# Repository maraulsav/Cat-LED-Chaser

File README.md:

# Cat-LED-Chaser
Hii! This is a cat shaped LED chaser. I wanted to make it as a keychain to be gifted to someone special for me during my highschool graduation later..
This is the final form of my cat LED casher

And here's the youtube video of my journey making this cat LED casher: https://www.youtube.com/watch?v=RgV0-7eemWM
See full built documentation at JOURNAL (1).md

## 3D View
Front

Back

## Features
- NE555P (555 Timer)
- CD4017 (Integrated Circuit)
- 10 LEDs
- 2 Capacitor
- 2 Resistor
- 1 Variable Resistor
- 1 Slide witch
- 1 Battery Socket
- 1 Battery

## PCB
My PCB is made in KiCad These are the footprints I used
- Battery: Battery_Panasonic_CR2032-HFN_Horizontal_CircularHoles
- Capacitor_THT:CP_Radial D5.0mm_P2.00mm
- LED_THT:LED_D3.0mm
- Resistor_THT:R_Axial_DIN0207_L6.3mm_D2.5mm_P7.62mm_Horizontal
- Variable Resistor: Potentiometer_THT: Potentiometer_Vishay_T93YA_Vertical
- SW SPST: Button_Switch_THT_SPST:SW_Push_1P2T_Vertical_E-Switch_800UDP8P1A1M6
- TestPoint: Connector PinSocket 2.54mm:PinSocket 1x01 P2.54mm Vertical
- NE555P: Package_DIP: DIP-8_W7.62mm
- 4017: footprints: N16

Here is my schematic:

and my PCB:

## BOM
You can see the BOM in Blinky Board-bom.csv files

## Additional Thingy
Thankyou for HackClub and  KiCad for making this project possible

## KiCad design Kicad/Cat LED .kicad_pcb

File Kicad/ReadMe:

Here's all the KiCad files. 
If you want to built your own LED chaser you can use my schematic design here!

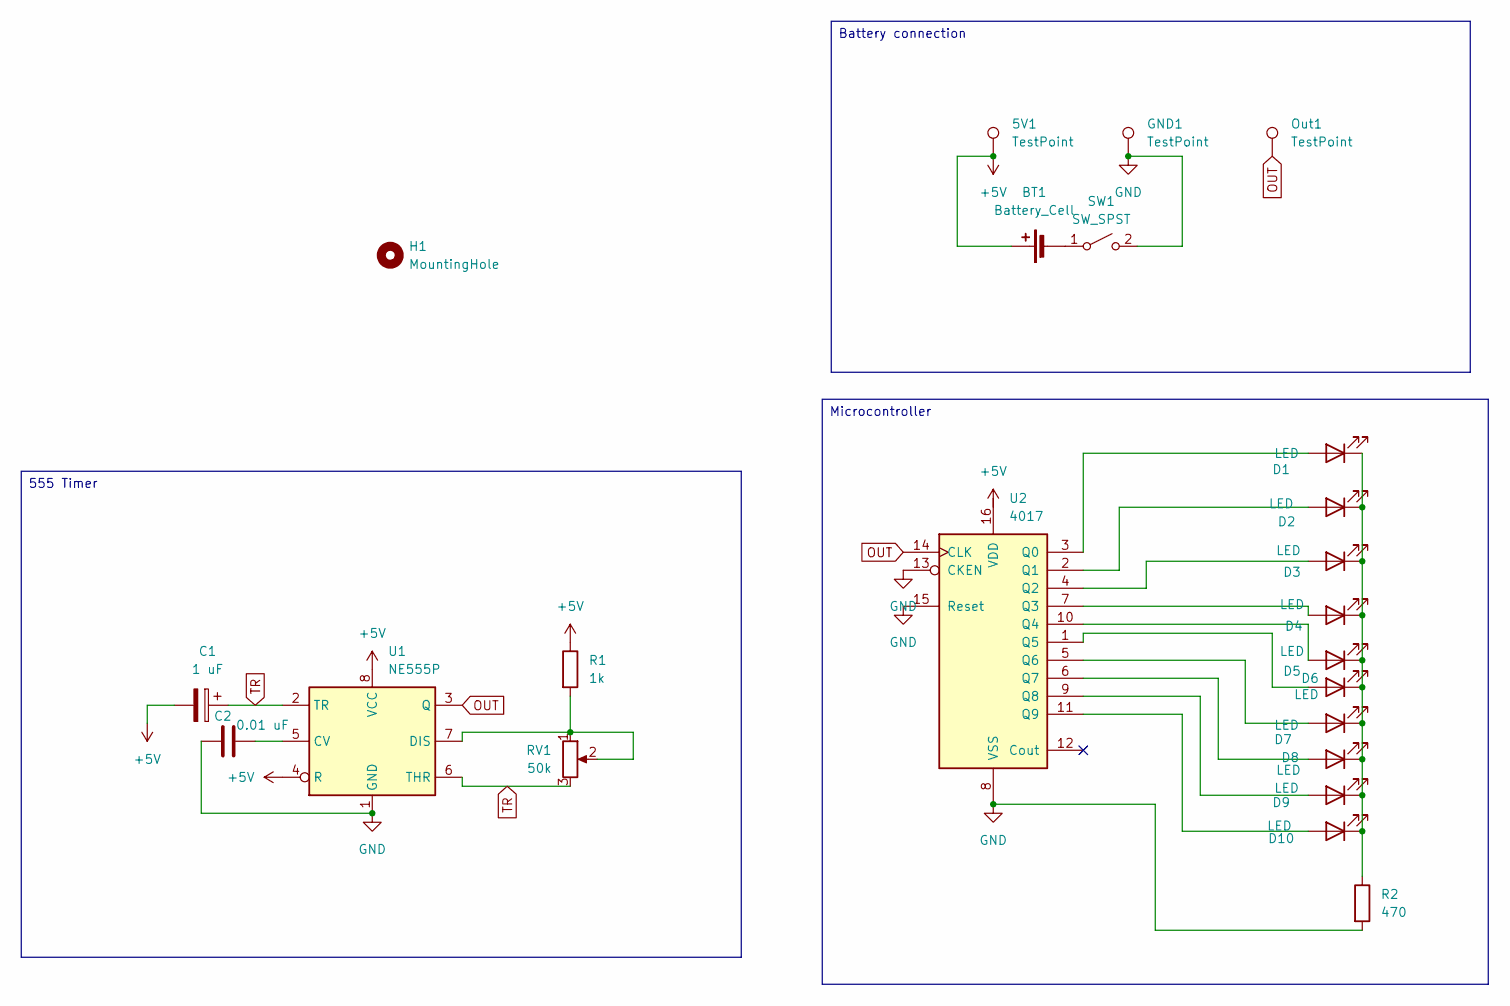
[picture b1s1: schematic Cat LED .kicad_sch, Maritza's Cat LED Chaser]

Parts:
5V1: TestPoint; PinSocket_1x01_P2.54mm_Vertical
BT1: Battery_Cell; Battery_Panasonic_CR2032-HFN_Horizontal_CircularHoles
C1: 1 uF; CP_Radial_D5.0mm_P2.00mm
C2: 0.01 uF; CP_Radial_D5.0mm_P2.00mm
D1, D2, D3, D4, D5, D6, D7, D8, D9, D10: LED; LED_D3.0mm
GND1: TestPoint; PinSocket_1x01_P2.54mm_Vertical
H1: MountingHole; MountingHole_4mm
Out1: TestPoint; PinSocket_1x01_P2.54mm_Vertical
R1: 1k; R_Axial_DIN0207_L6.3mm_D2.5mm_P7.62mm_Horizontal
R2: 470; R_Axial_DIN0207_L6.3mm_D2.5mm_P7.62mm_Horizontal
RV1: 50k; Potentiometer_Vishay_T93YA_Vertical
SW1: SW_SPST; SW_Push_1P2T_Vertical_E-Switch_800UDP8P1A1M6
U1: NE555P; DIP-8_W7.62mm
U2: 4017; N16

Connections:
+5V: 5V1.1, BT1.1 (+), C1.2, R1.1, U1.4 (R), U1.8 (VCC)
GND: C2.2, GND1.1, R2.2, SW1.2 (B), U1.1 (GND), U2.8 (VSS), U2.13 (CKEN), U2.15 (Reset)
unnamed: BT1.2 (-), SW1.1 (A)
unnamed: D1.2 (A), U2.3 (Q0)
unnamed: D1.1 (K), D2.1 (K), D3.1 (K), D4.1 (K), D5.1 (K), D6.1 (K), D7.1 (K), D8.1 (K), D9.1 (K), D10.1 (K), R2.1
unnamed: D2.2 (A), U2.2 (Q1)
unnamed: D3.2 (A), U2.4 (Q2)
unnamed: D4.2 (A), U2.7 (Q3)
unnamed: D5.2 (A), U2.10 (Q4)
unnamed: D6.2 (A), U2.1 (Q5)
unnamed: D7.2 (A), U2.5 (Q6)
unnamed: D8.2 (A), U2.6 (Q7)
unnamed: D9.2 (A), U2.9 (Q8)
unnamed: D10.2 (A), U2.11 (Q9)
unnamed: C2.1, U1.5 (CV)
unnamed: R1.2, RV1.1, RV1.2, U1.7 (DIS)
OUT: Out1.1, U1.3 (Q), U2.14 (CLK)
TR: C1.1, RV1.3, U1.2 (TR), U1.6 (THR)

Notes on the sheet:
Microcontroller
Battery connection
555 Timer

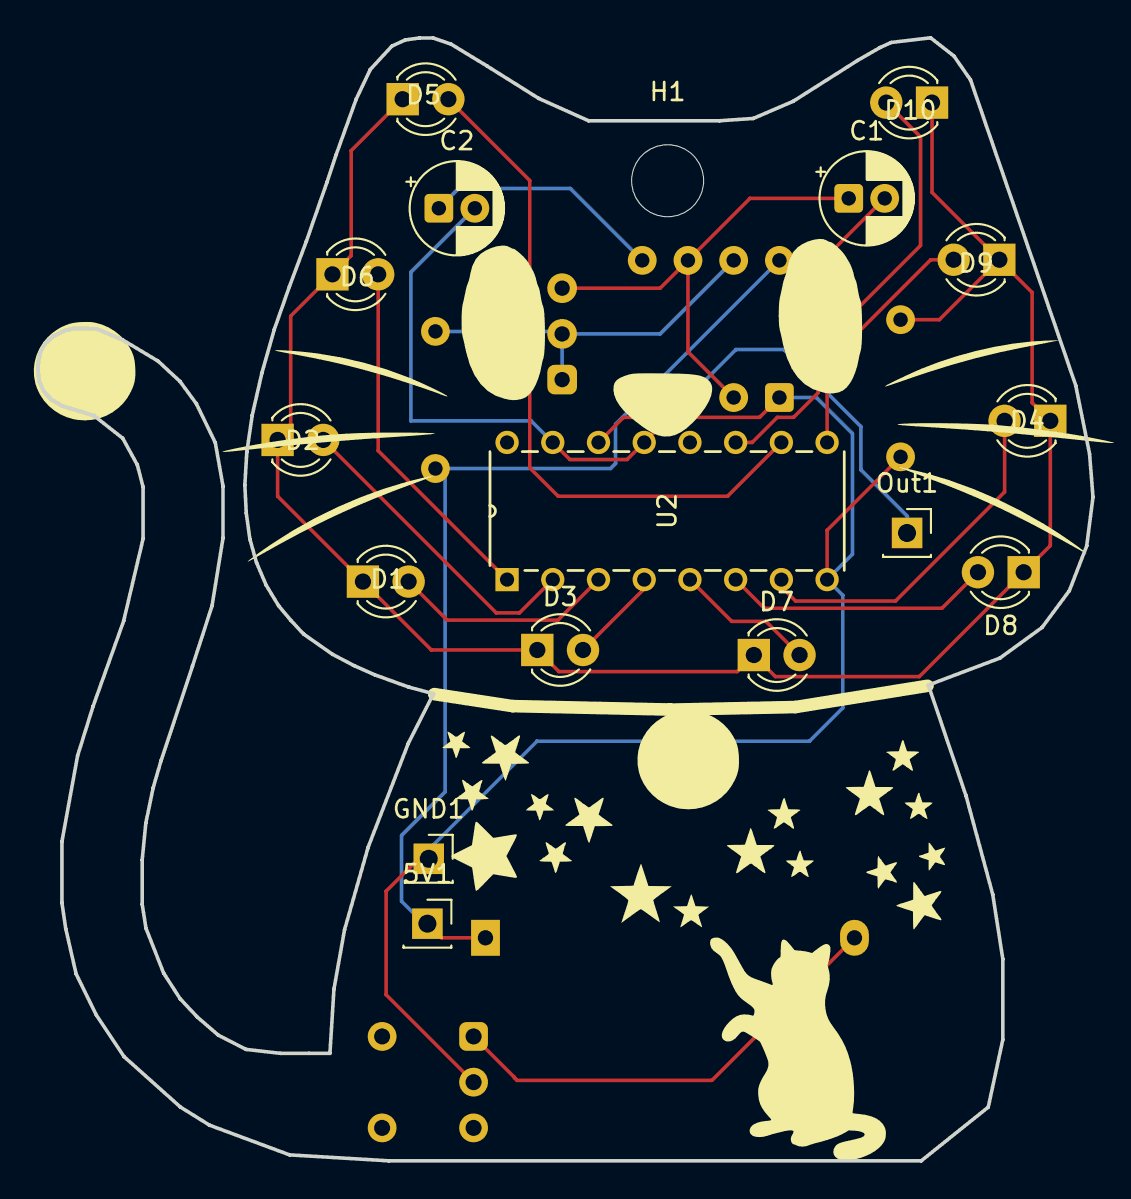
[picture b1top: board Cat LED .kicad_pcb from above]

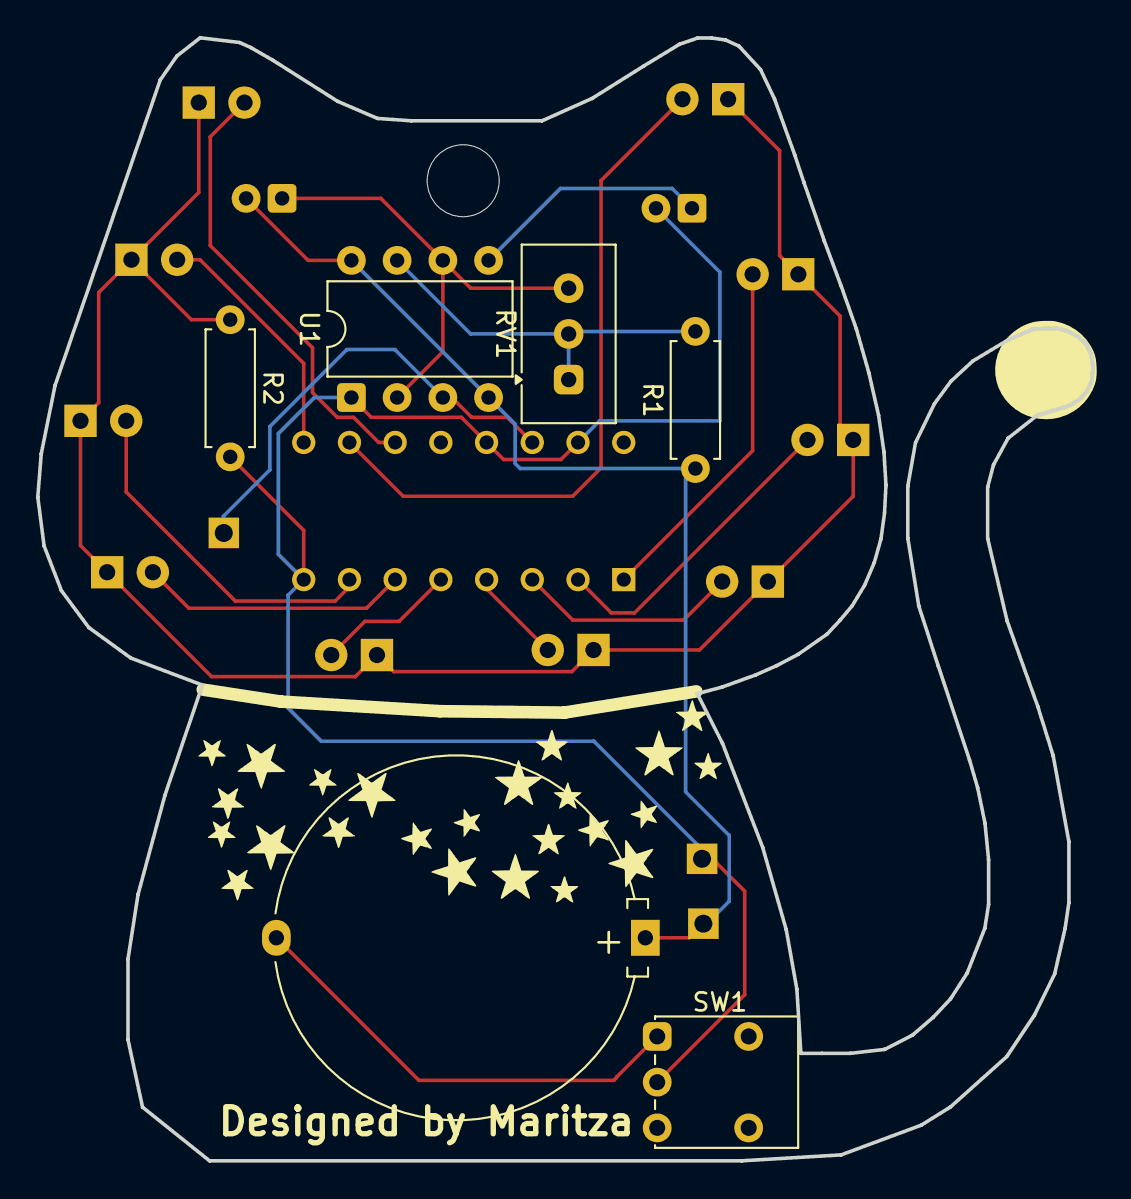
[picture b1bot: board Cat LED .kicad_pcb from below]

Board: 2 copper layers, 58.6 x 62.4 mm, 23 parts (6 on the bottom side), 18 nets.
